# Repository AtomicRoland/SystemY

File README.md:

# SystemY
A keyboard, display and cassette interface for the Yarrb2 board.

When I designed the Yarrb2 board I kept in mind that it should be possible to use the board as a stand-alone system. Back then I already set my mind on making it some kind of System 1 clone. I explicitly say that this is a System1 clone and not a replica because the hardware doesn't look anything like an original System 1. Besides the original options like 1152 bytes RAM, 512 bytes ROM, 300 baud cassette, eight character display and 25 keys this version has the following additional options:

* The memory can be expanded to (almost) 60KB RAM and 4KB ROM (in the current CPLD version, you can of course expand it to 128K + 128K but that seems a bit overdone to me)
* RAM between #8000 - #EFFF can be write protected
* The reset button can be configured to generate an NMI or IRQ
* You have access to eight useless LEDs (because they are on the back side of the system)
* With a suitable CPU this system can run at 1, 2 of 4MHz
* The cassette output can be programmed to act like the Atom 1-bit audio

The cassette in-out is the most difficult part of the project and this is not working yet. I can output a 1200Hz and 2400Hz tone by clearing or setting bit 6 of port A (#E20) and when I save a block of data it sounds like there is a data stream. However, a connected Atom cannot load the data. Also writing to tape and reading back does not work. The CPLD will reset bit 7 of #E20 to 0 when there is a 1200Hz tone at the cassette input and set that bit to 1 if there is a 2400Hz tone. But reading data from an Atom, recorded tape or WAV file does not work although the signal looks nice on my oscilloscope.

And of course I had a lot of design mistakes on this board :shock: I forgot a series resistor for each digit, swapped inputs of the LM358 and I swapped the in and out of the cassette connector. Since I don't expect that somebody wants such a board I didn't mention it, but I record it here just to not forget these issues....

The KiCad files contain the diagram (also in PDF) and the gerber files.

## Copyright and disclosure

You are free to copy and use these files as you want to. However, I don't guarantee any support for your own projects.

The hardware and software in this project are as-is. No warranties, use at your own risk and do not use these in medical or life-supporting devices. Please don't blame me if something goes wrong.

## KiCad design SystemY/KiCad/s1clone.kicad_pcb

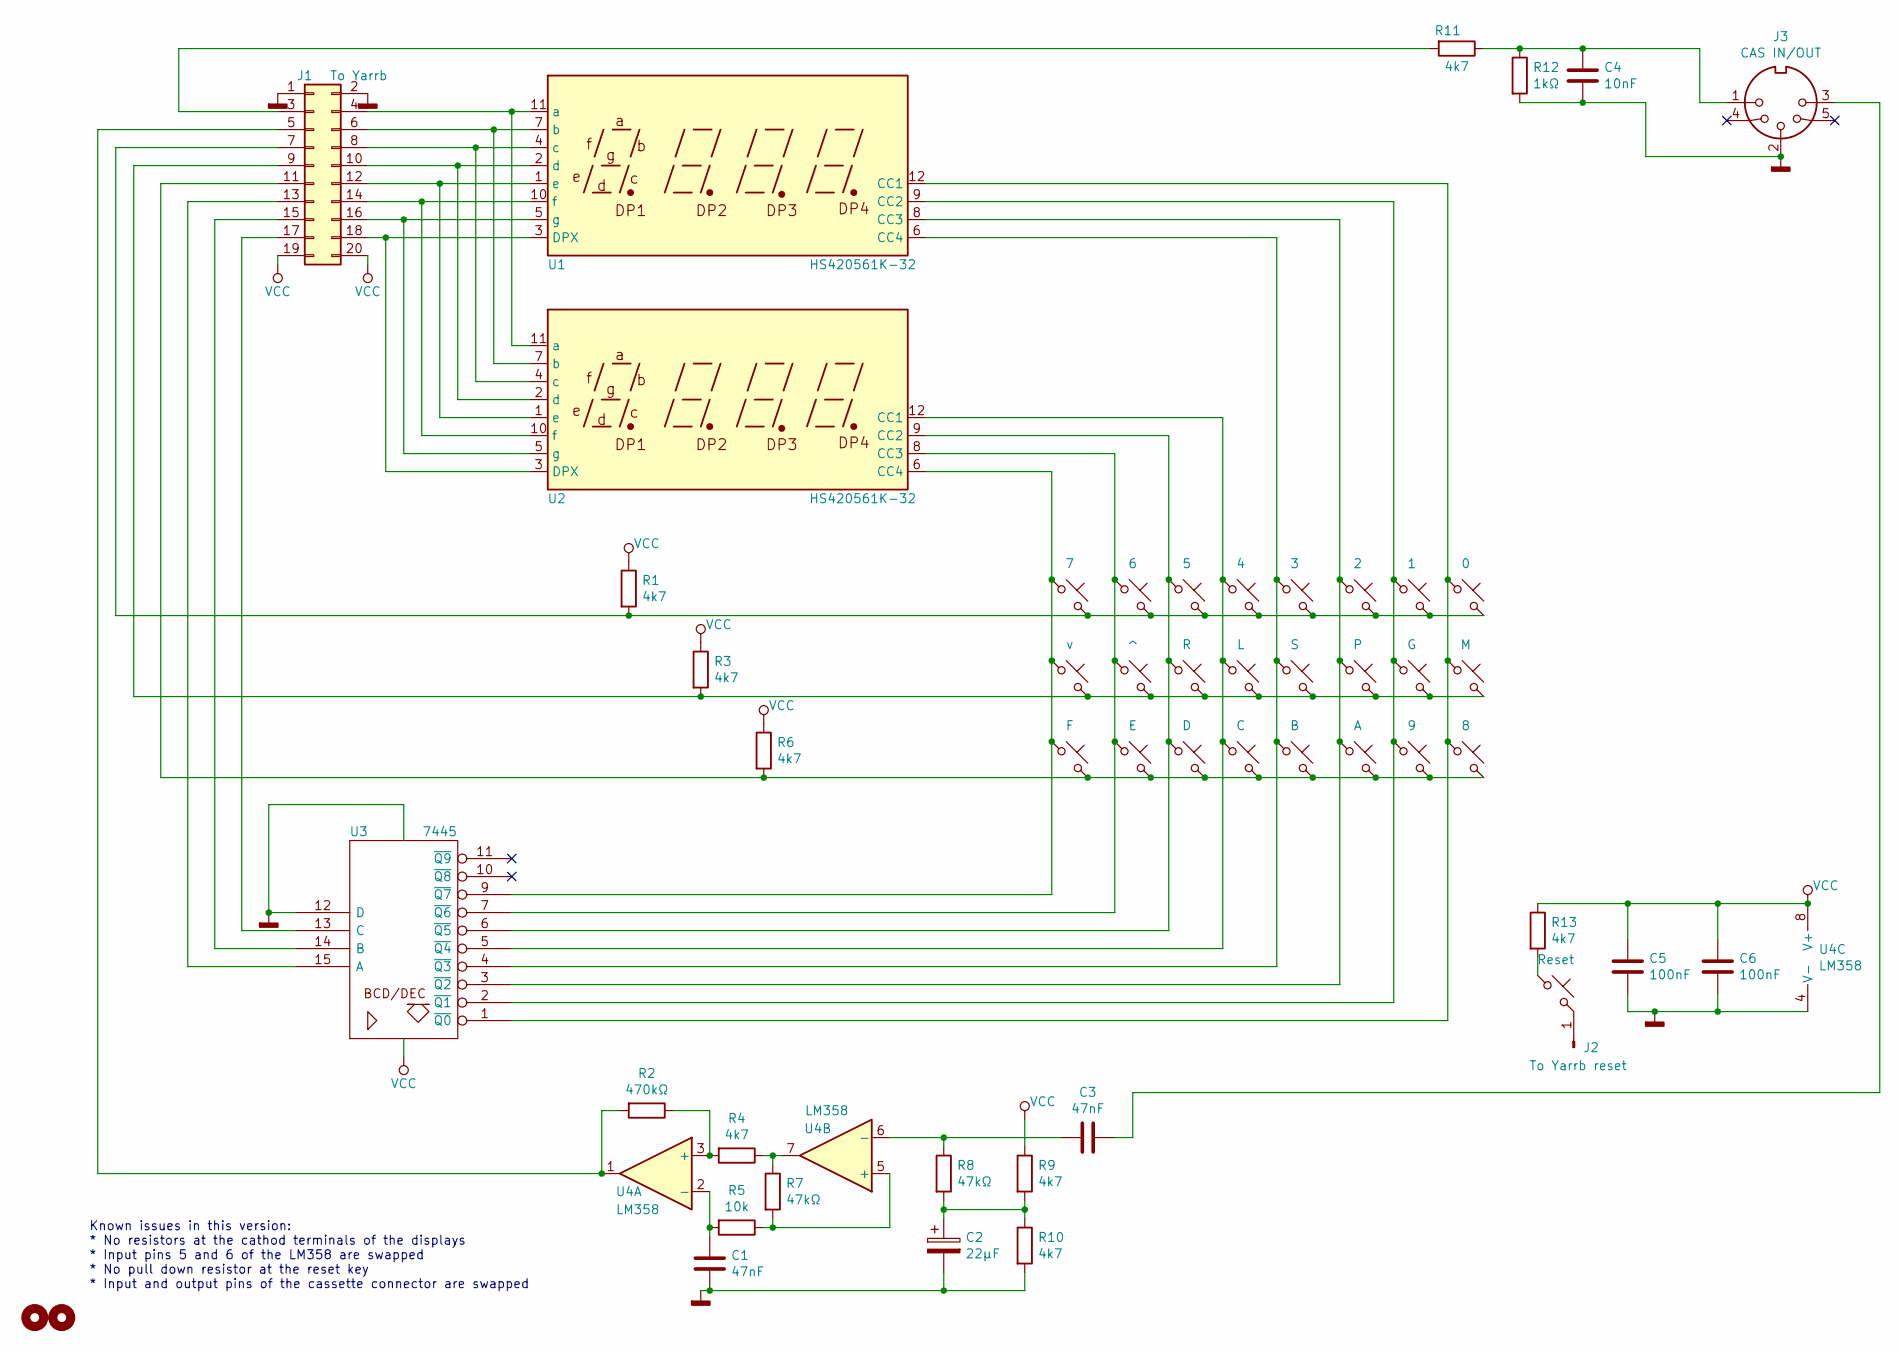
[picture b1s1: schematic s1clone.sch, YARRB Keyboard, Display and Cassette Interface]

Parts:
C1, C3: 47nF; C_Rect_L7.0mm_W3.5mm_P5.00mm
C2: 22µF; CP_Radial_D6.3mm_P2.50mm
C4: 10nF; C_Rect_L7.0mm_W3.5mm_P5.00mm
C5, C6: 100nF; C_Rect_L7.0mm_W3.5mm_P5.00mm
H1, H2: MountingHole; MountingHole_2.2mm_M2
J1: To Yarrb; PinHeader_2x10_P2.54mm_Vertical
J2: To Yarrb reset; PinHeader_1x01_P2.54mm_Vertical
J3: CAS IN/OUT; din-5
R1, R3, R4, R6, R9, R10, R11, R13: 4k7; R_Axial_DIN0411_L9.9mm_D3.6mm_P15.24mm_Horizontal
R2: 470kΩ; R_Axial_DIN0411_L9.9mm_D3.6mm_P15.24mm_Horizontal
R5: 10k; R_Axial_DIN0411_L9.9mm_D3.6mm_P15.24mm_Horizontal
R7, R8: 47kΩ; R_Axial_DIN0411_L9.9mm_D3.6mm_P15.24mm_Horizontal
R12: 1kΩ; R_Axial_DIN0411_L9.9mm_D3.6mm_P15.24mm_Horizontal
SW1: 7; SW_PUSH-12mm
SW2: v; SW_PUSH-12mm
SW3: F; SW_PUSH-12mm
SW4: 6; SW_PUSH-12mm
SW5: ^; SW_PUSH-12mm
SW6: E; SW_PUSH-12mm
SW7: 5; SW_PUSH-12mm
SW8: R; SW_PUSH-12mm
SW9: D; SW_PUSH-12mm
SW10: 4; SW_PUSH-12mm
SW11: L; SW_PUSH-12mm
SW12: C; SW_PUSH-12mm
SW13: 3; SW_PUSH-12mm
SW14: S; SW_PUSH-12mm
SW15: B; SW_PUSH-12mm
SW16: 2; SW_PUSH-12mm
SW17: P; SW_PUSH-12mm
SW18: A; SW_PUSH-12mm
SW19: 1; SW_PUSH-12mm
SW20: G; SW_PUSH-12mm
SW21: 9; SW_PUSH-12mm
SW22: 0; SW_PUSH-12mm
SW23: M; SW_PUSH-12mm
SW24: 8; SW_PUSH-12mm
SW25: Reset; SW_PUSH-12mm
U1, U2: HS420561K-32; CC56-12GWA
U3: 7445; DIP-16_W7.62mm_Socket
U4: LM358; DIP-8_W7.62mm_Socket

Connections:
GND: C1.2, C2.2, C4.2, C5.1, C6.1, J1.1, J1.2, J3.2, R10.2, R12.2, U3.8 (GND), U3.12 (D), U4.4 (V-)
unnamed: C1.1, R5.2, U4.2 (-)
unnamed: C2.1, R8.2, R9.2, R10.1
unnamed: C3.1, J3.3
unnamed: C3.2, R8.1, U4.6 (-)
unnamed: C4.1, J3.1, R11.1, R12.1
unnamed: J1.3, R11.2
unnamed: J1.4, U1.11 (a), U2.11 (a)
unnamed: J1.5, R2.2, U4.1
unnamed: J1.6, U1.7 (b), U2.7 (b)
unnamed: J1.7, R1.2, SW1.2, SW4.2, SW7.2, SW10.2, SW13.2, SW16.2, SW19.2, SW22.2
unnamed: J1.8, U1.4 (c), U2.4 (c)
unnamed: J1.9, R3.2, SW2.2, SW5.2, SW8.2, SW11.2, SW14.2, SW17.2, SW20.2, SW23.2
unnamed: J1.10, U1.2 (d), U2.2 (d)
unnamed: J1.11, R6.2, SW3.2, SW6.2, SW9.2, SW12.2, SW15.2, SW18.2, SW21.2, SW24.2
unnamed: J1.12, U1.1 (e), U2.1 (e)
unnamed: J1.13, U3.15 (A)
unnamed: J1.14, U1.10 (f), U2.10 (f)
unnamed: J1.15, U3.14 (B)
unnamed: J1.16, U1.5 (g), U2.5 (g)
unnamed: J1.17, U3.13 (C)
unnamed: J1.18, U1.3 (DPX), U2.3 (DPX)
unnamed: J2.1, SW25.2
unnamed: R2.1, R4.2, U4.3 (+)
unnamed: R4.1, R7.1, U4.7
unnamed: R5.1, R7.2, U4.5 (+)
unnamed: R13.2, SW25.1
unnamed: SW1.1, SW2.1, SW3.1, U2.6 (CC4), U3.9 (~Q7)
unnamed: SW4.1, SW5.1, SW6.1, U2.8 (CC3), U3.7 (~Q6)
unnamed: SW7.1, SW8.1, SW9.1, U2.9 (CC2), U3.6 (~Q5)
unnamed: SW10.1, SW11.1, SW12.1, U2.12 (CC1), U3.5 (~Q4)
unnamed: SW13.1, SW14.1, SW15.1, U1.6 (CC4), U3.4 (~Q3)
unnamed: SW16.1, SW17.1, SW18.1, U1.8 (CC3), U3.3 (~Q2)
unnamed: SW19.1, SW20.1, SW21.1, U1.9 (CC2), U3.2 (~Q1)
unnamed: SW22.1, SW23.1, SW24.1, U1.12 (CC1), U3.1 (~Q0)
VCC: C5.2, C6.2, J1.19, J1.20, R1.1, R3.1, R6.1, R9.1, R13.1, U3.16 (VCC), U4.8 (V+)

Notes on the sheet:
Known issues in this version: * No resistors at the cathod terminals of the displays * Input pins 5 and 6 of the LM358 are swapped * No pull down resistor at the reset key * Input and output pins of the cassette connector are swapped

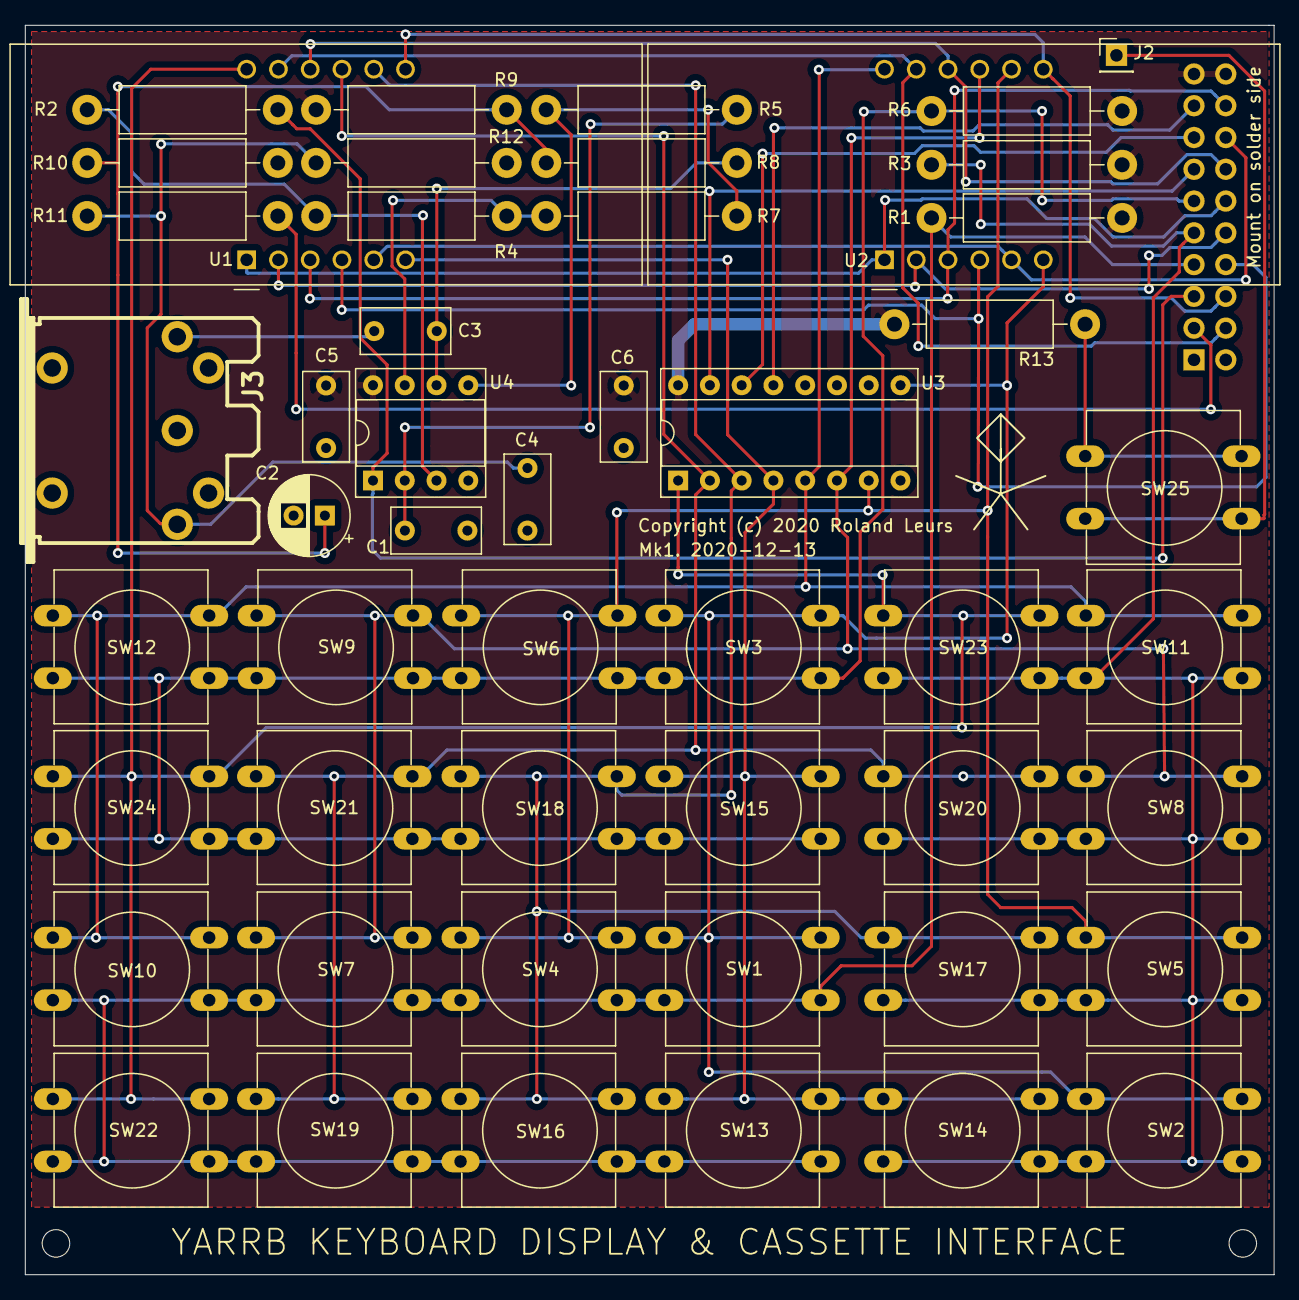
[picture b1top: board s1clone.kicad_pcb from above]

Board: 2 copper layers, 99.9 x 99.9 mm, 53 parts (1 on the bottom side), 36 nets.

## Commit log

2020-12-31 Initial upload of project files
2020-12-31 Update README.md
    Added a project description.

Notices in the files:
SystemY/KiCad/s1clone.kicad_pcb:
Copyright (c) 2020 Roland Leurs
